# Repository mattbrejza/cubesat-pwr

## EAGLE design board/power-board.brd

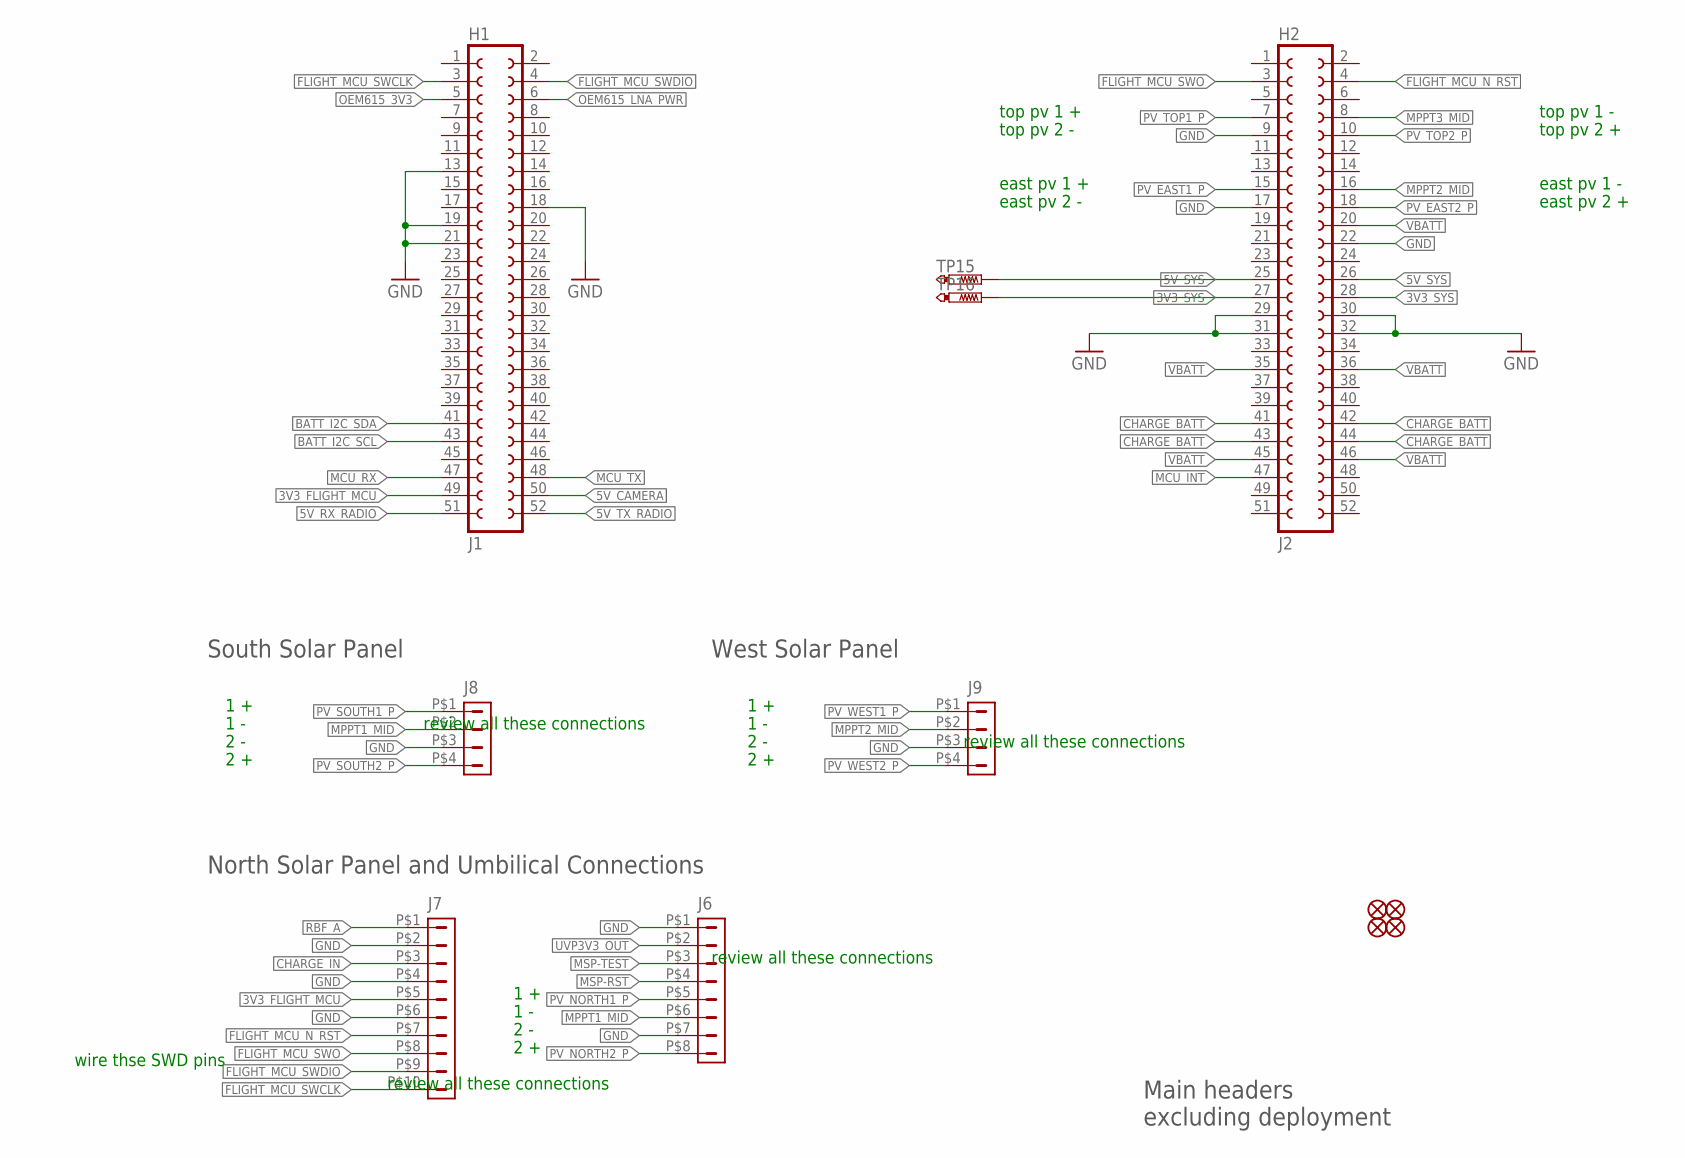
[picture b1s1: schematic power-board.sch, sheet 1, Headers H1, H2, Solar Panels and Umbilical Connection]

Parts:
FID1, FID2, FID3, FID4: FIDUCIAL1X2-STOP; FIDUCIAL-1X2-STOP
J1: H1; FE26-2
J2: H2; FE26-2
J6: DF13-8P-1.25DS
J7: DF13-10P-1.25DS
J8, J9: DF13-4P-1.25DS
TP15, TP16: PTR1TP09R; TP09R

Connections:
3V3_FLIGHT_MCU: J1.49, J7.P$5 (5); also elsewhere on the board
3V3_SYS: J2.27, J2.28, TP16.TP; also elsewhere on the board
5V_CAMERA: J1.50; also elsewhere on the board
5V_RX_RADIO: J1.51; also elsewhere on the board
5V_SYS: J2.25, J2.26, TP15.TP; also elsewhere on the board
5V_TX_RADIO: J1.52; also elsewhere on the board
BATT_I2C_SCL: J1.43; also elsewhere on the board
BATT_I2C_SDA: J1.41; also elsewhere on the board
CHARGE_BATT: J2.41, J2.42, J2.43, J2.44; also elsewhere on the board
CHARGE_IN: J7.P$3 (3); also elsewhere on the board
FLIGHT_MCU_N_RST: J2.4, J7.P$7 (7)
FLIGHT_MCU_SWCLK: J1.3, J7.P$10 (10)
FLIGHT_MCU_SWDIO: J1.4, J7.P$9 (9)
FLIGHT_MCU_SWO: J2.3, J7.P$8 (8)
GND: J1.13, J1.18, J1.19, J1.21, J2.9, J2.17, J2.22, J2.29, J2.30, J2.31, J2.32, J6.P$1 (1), J6.P$7 (7), J7.P$2 (2), J7.P$4 (4), J7.P$6 (6), J8.P$3 (3), J9.P$3 (3); also elsewhere on the board
MCU_INT: J2.47; also elsewhere on the board
MCU_RX: J1.47; also elsewhere on the board
MCU_TX: J1.48; also elsewhere on the board
MPPT1_MID: J6.P$6 (6), J8.P$2 (2); also elsewhere on the board
MPPT2_MID: J2.16, J9.P$2 (2); also elsewhere on the board
MPPT3_MID: J2.8; also elsewhere on the board
MSP-RST: J6.P$4 (4); also elsewhere on the board
MSP-TEST: J6.P$3 (3); also elsewhere on the board
OEM615_3V3: J1.5; also elsewhere on the board
OEM615_LNA_PWR: J1.6; also elsewhere on the board
PV_EAST1_P: J2.15; also elsewhere on the board
PV_EAST2_P: J2.18; also elsewhere on the board
PV_NORTH1_P: J6.P$5 (5); also elsewhere on the board
PV_NORTH2_P: J6.P$8 (8); also elsewhere on the board
PV_SOUTH1_P: J8.P$1 (1); also elsewhere on the board
PV_SOUTH2_P: J8.P$4 (4); also elsewhere on the board
PV_TOP1_P: J2.7; also elsewhere on the board
PV_TOP2_P: J2.10; also elsewhere on the board
PV_WEST1_P: J9.P$1 (1); also elsewhere on the board
PV_WEST2_P: J9.P$4 (4); also elsewhere on the board
RBF_A: J7.P$1 (1)
UVP3V3_OUT: J6.P$2 (2); also elsewhere on the board
VBATT: J2.20, J2.35, J2.36, J2.45, J2.46; also elsewhere on the board

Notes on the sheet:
South Solar Panel
West Solar Panel
North Solar Panel and Umbilical Connections
Main headers excluding deployment
review all these connections
top pv 1 -
east pv 1 -
east pv 2 +
top pv 2 +
wire thse SWD pins
top pv 1 +
top pv 2 -
east pv 1 +
east pv 2 -
1 +
1 -
2 +
2 -

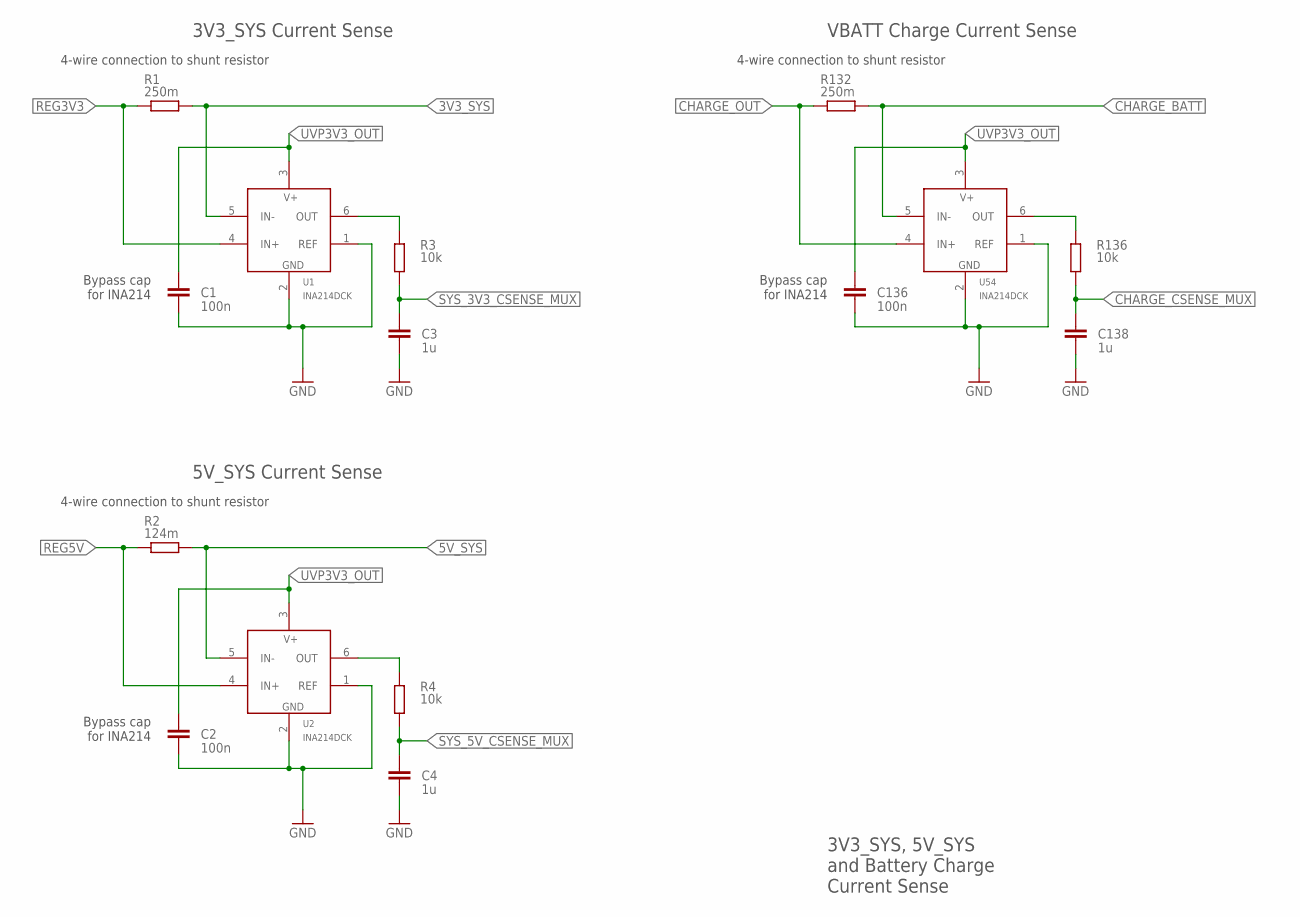
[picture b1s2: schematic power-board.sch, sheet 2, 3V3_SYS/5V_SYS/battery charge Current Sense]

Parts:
C1, C2, C136: 100n; C0603
C3, C4, C138: 1u; C0603
R1, R132: 250m; R1206
R2: 124m; R1206
R3, R4, R136: 10k; R0603
U1, U2, U54: INA214DCK; SC70-6

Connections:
3V3_SYS: R1.2, U1.5 (IN-); also elsewhere on the board
5V_SYS: R2.2, U2.5 (IN-); also elsewhere on the board
CHARGE_BATT: R132.2, U54.5 (IN-); also elsewhere on the board
CHARGE_CSENSE_MUX: C138.1, R136.1; also elsewhere on the board
CHARGE_OUT: R132.1, U54.4 (IN+); also elsewhere on the board
GND: C1.2, C2.2, C3.2, C4.2, C136.2, C138.2, U1.1 (REF), U1.2 (GND), U2.1 (REF), U2.2 (GND), U54.1 (REF), U54.2 (GND); also elsewhere on the board
unnamed: R3.2, U1.6 (OUT)
unnamed: R4.2, U2.6 (OUT)
unnamed: R136.2, U54.6 (OUT)
REG3V3: R1.1, U1.4 (IN+); also elsewhere on the board
REG5V: R2.1, U2.4 (IN+); also elsewhere on the board
SYS_3V3_CSENSE_MUX: C3.1, R3.1; also elsewhere on the board
SYS_5V_CSENSE_MUX: C4.1, R4.1; also elsewhere on the board
UVP3V3_OUT: C1.1, C2.1, C136.1, U1.3 (V+), U2.3 (V+), U54.3 (V+); also elsewhere on the board

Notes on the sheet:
4-wire connection to shunt resistor
Bypass cap for INA214
3V3_SYS, 5V_SYS and Battery Charge Current Sense
3V3_SYS Current Sense
5V_SYS Current Sense
VBATT Charge Current Sense

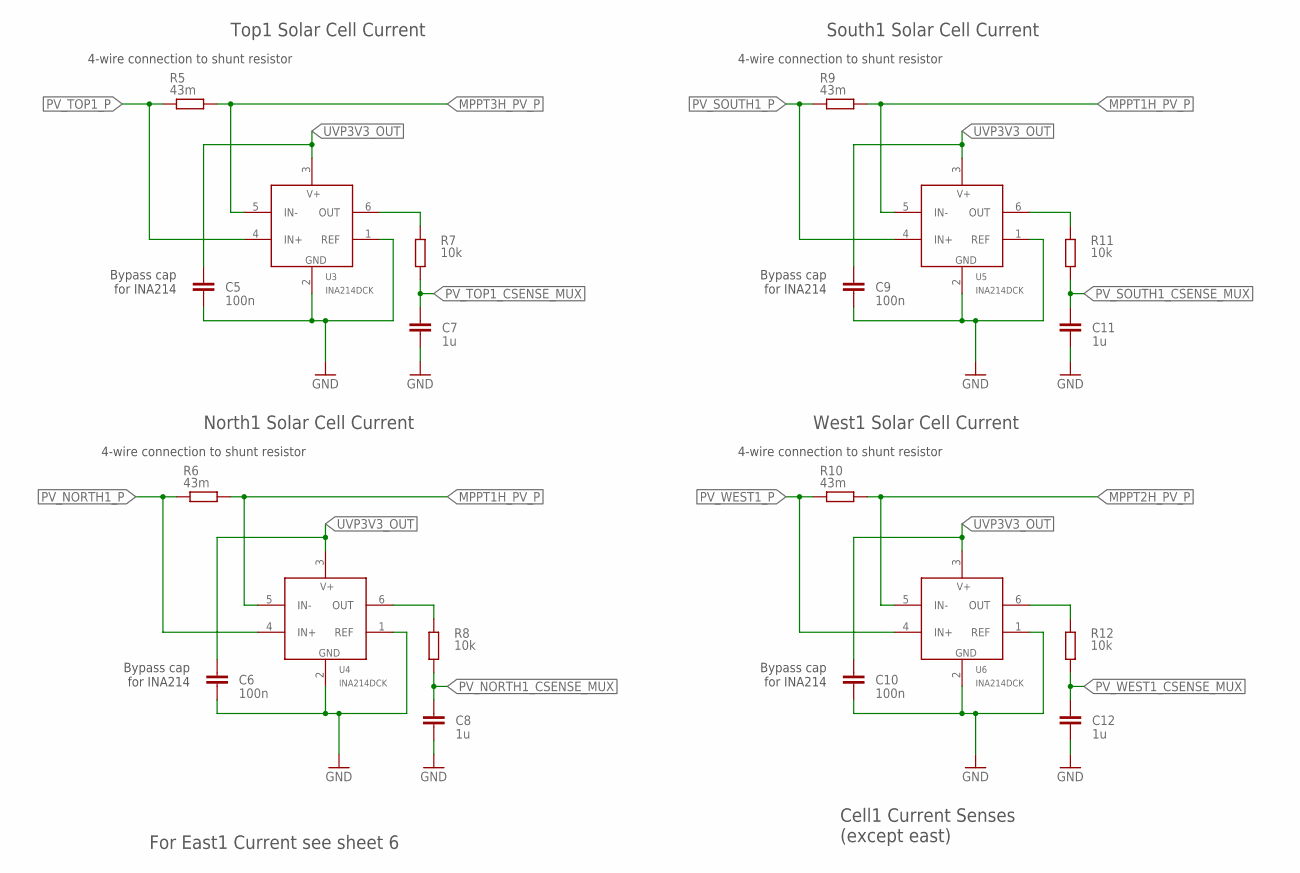
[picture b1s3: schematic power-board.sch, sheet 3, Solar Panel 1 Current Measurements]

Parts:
C5, C6, C9, C10: 100n; C0603
C7, C8, C11, C12: 1u; C0603
R5, R6, R9, R10: 43m; R1206
R7, R8, R11, R12: 10k; R0603
U3, U4, U5, U6: INA214DCK; SC70-6

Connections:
GND: C5.2, C6.2, C7.2, C8.2, C9.2, C10.2, C11.2, C12.2, U3.1 (REF), U3.2 (GND), U4.1 (REF), U4.2 (GND), U5.1 (REF), U5.2 (GND), U6.1 (REF), U6.2 (GND); also elsewhere on the board
MPPT1H_PV_P: R6.2, R9.2, U4.5 (IN-), U5.5 (IN-); also elsewhere on the board
MPPT2H_PV_P: R10.2, U6.5 (IN-); also elsewhere on the board
MPPT3H_PV_P: R5.2, U3.5 (IN-); also elsewhere on the board
unnamed: R7.2, U3.6 (OUT)
unnamed: R11.2, U5.6 (OUT)
unnamed: R8.2, U4.6 (OUT)
unnamed: R12.2, U6.6 (OUT)
PV_NORTH1_CSENSE_MUX: C8.1, R8.1; also elsewhere on the board
PV_NORTH1_P: R6.1, U4.4 (IN+); also elsewhere on the board
PV_SOUTH1_CSENSE_MUX: C11.1, R11.1; also elsewhere on the board
PV_SOUTH1_P: R9.1, U5.4 (IN+); also elsewhere on the board
PV_TOP1_CSENSE_MUX: C7.1, R7.1; also elsewhere on the board
PV_TOP1_P: R5.1, U3.4 (IN+); also elsewhere on the board
PV_WEST1_CSENSE_MUX: C12.1, R12.1; also elsewhere on the board
PV_WEST1_P: R10.1, U6.4 (IN+); also elsewhere on the board
UVP3V3_OUT: C5.1, C6.1, C9.1, C10.1, U3.3 (V+), U4.3 (V+), U5.3 (V+), U6.3 (V+); also elsewhere on the board

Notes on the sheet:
4-wire connection to shunt resistor
Bypass cap for INA214
Top1 Solar Cell Current
South1 Solar Cell Current
North1 Solar Cell Current
Cell1 Current Senses (except east)
West1 Solar Cell Current
For East1 Current see sheet 6

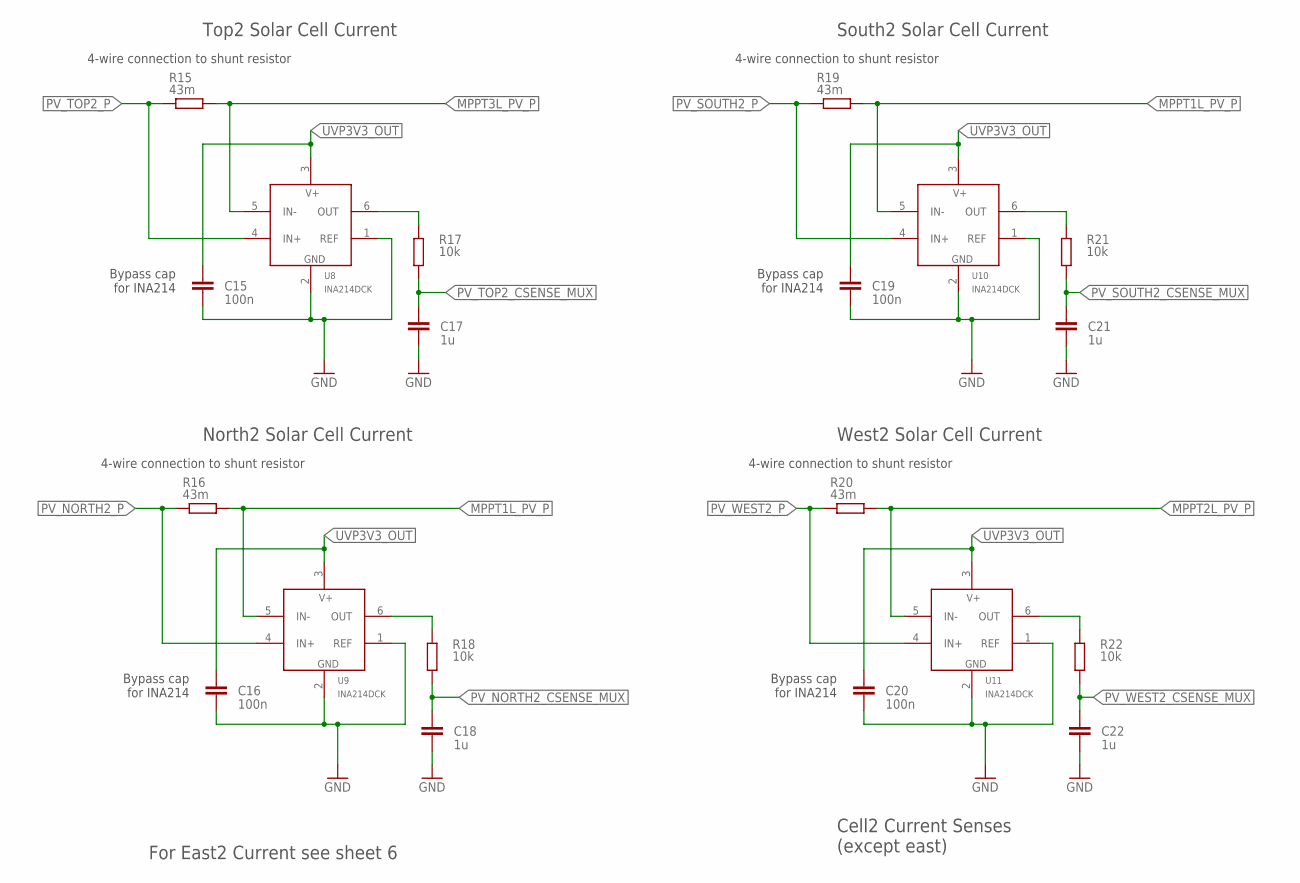
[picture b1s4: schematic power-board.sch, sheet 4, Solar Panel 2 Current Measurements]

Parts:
C15, C16, C19, C20: 100n; C0603
C17, C18, C21, C22: 1u; C0603
R15, R16, R19, R20: 43m; R1206
R17, R18, R21, R22: 10k; R0603
U8, U9, U10, U11: INA214DCK; SC70-6

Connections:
GND: C15.2, C16.2, C17.2, C18.2, C19.2, C20.2, C21.2, C22.2, U8.1 (REF), U8.2 (GND), U9.1 (REF), U9.2 (GND), U10.1 (REF), U10.2 (GND), U11.1 (REF), U11.2 (GND); also elsewhere on the board
MPPT1L_PV_P: R16.2, R19.2, U9.5 (IN-), U10.5 (IN-); also elsewhere on the board
MPPT2L_PV_P: R20.2, U11.5 (IN-); also elsewhere on the board
MPPT3L_PV_P: R15.2, U8.5 (IN-); also elsewhere on the board
unnamed: R17.2, U8.6 (OUT)
unnamed: R21.2, U10.6 (OUT)
unnamed: R18.2, U9.6 (OUT)
unnamed: R22.2, U11.6 (OUT)
PV_NORTH2_CSENSE_MUX: C18.1, R18.1; also elsewhere on the board
PV_NORTH2_P: R16.1, U9.4 (IN+); also elsewhere on the board
PV_SOUTH2_CSENSE_MUX: C21.1, R21.1; also elsewhere on the board
PV_SOUTH2_P: R19.1, U10.4 (IN+); also elsewhere on the board
PV_TOP2_CSENSE_MUX: C17.1, R17.1; also elsewhere on the board
PV_TOP2_P: R15.1, U8.4 (IN+); also elsewhere on the board
PV_WEST2_CSENSE_MUX: C22.1, R22.1; also elsewhere on the board
PV_WEST2_P: R20.1, U11.4 (IN+); also elsewhere on the board
UVP3V3_OUT: C15.1, C16.1, C19.1, C20.1, U8.3 (V+), U9.3 (V+), U10.3 (V+), U11.3 (V+); also elsewhere on the board

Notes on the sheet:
4-wire connection to shunt resistor
Bypass cap for INA214
Top2 Solar Cell Current
South2 Solar Cell Current
North2 Solar Cell Current
West2 Solar Cell Current
Cell2 Current Senses (except east)
For East2 Current see sheet 6

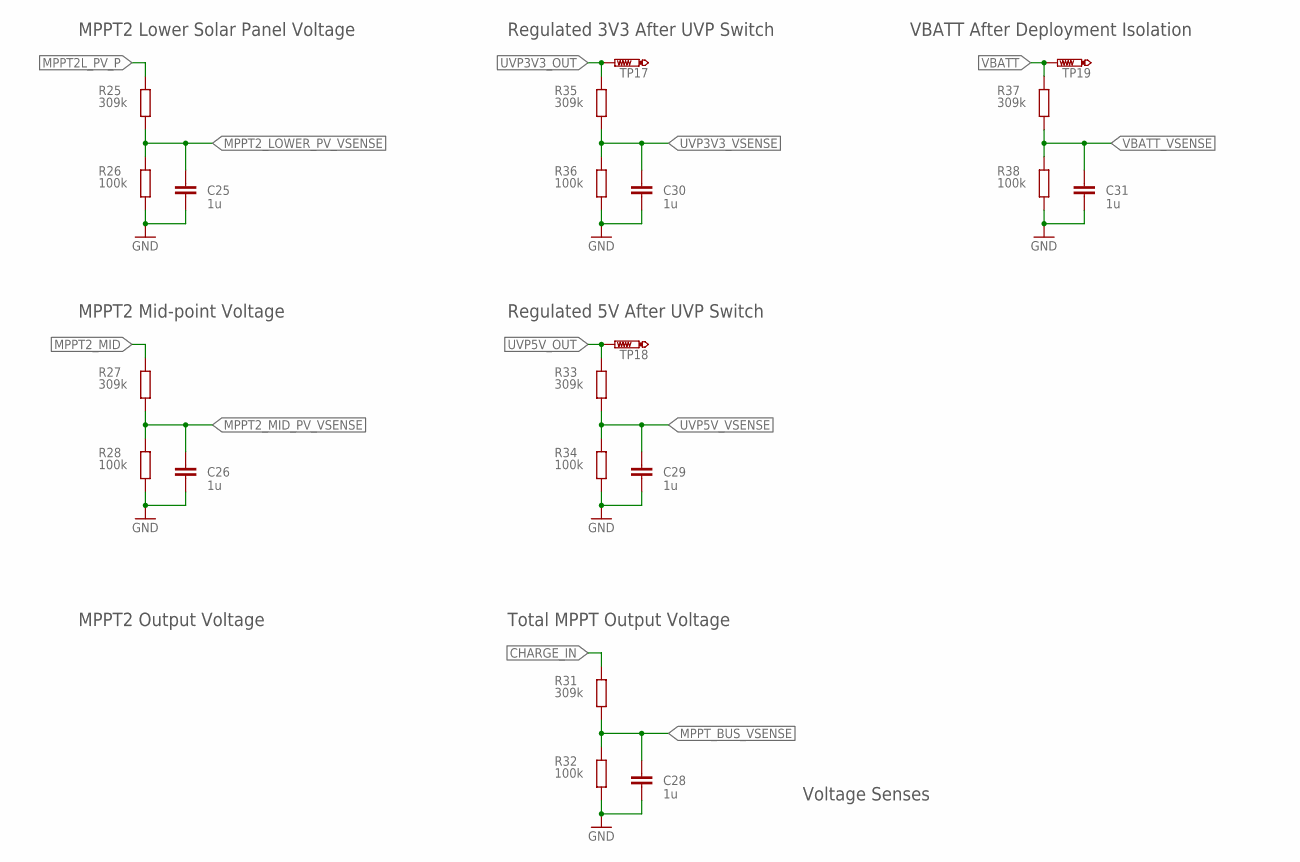
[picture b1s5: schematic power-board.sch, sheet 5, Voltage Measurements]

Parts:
C25, C26, C28, C29, C30, C31: 1u; C0603
R25, R27, R31, R33, R35, R37: 309k; R0603
R26, R28, R32, R34, R36, R38: 100k; R0603
TP17, TP18, TP19: PTR1TP09R; TP09R

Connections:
CHARGE_IN: R31.2; also elsewhere on the board
GND: C25.2, C26.2, C28.2, C29.2, C30.2, C31.2, R26.1, R28.1, R32.1, R34.1, R36.1, R38.1; also elsewhere on the board
MPPT2L_PV_P: R25.2; also elsewhere on the board
MPPT2_LOWER_PV_VSENSE: C25.1, R25.1, R26.2; also elsewhere on the board
MPPT2_MID: R27.2; also elsewhere on the board
MPPT2_MID_PV_VSENSE: C26.1, R27.1, R28.2; also elsewhere on the board
MPPT_BUS_VSENSE: C28.1, R31.1, R32.2; also elsewhere on the board
UVP3V3_OUT: R35.2, TP17.TP; also elsewhere on the board
UVP3V3_VSENSE: C30.1, R35.1, R36.2; also elsewhere on the board
UVP5V_OUT: R33.2, TP18.TP; also elsewhere on the board
UVP5V_VSENSE: C29.1, R33.1, R34.2; also elsewhere on the board
VBATT: R37.2, TP19.TP; also elsewhere on the board
VBATT_VSENSE: C31.1, R37.1, R38.2; also elsewhere on the board

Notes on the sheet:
MPPT2 Lower Solar Panel Voltage
MPPT2 Mid-point Voltage
Regulated 5V After UVP Switch
Regulated 3V3 After UVP Switch
MPPT2 Output Voltage
Total MPPT Output Voltage
VBATT After Deployment Isolation
Voltage Senses

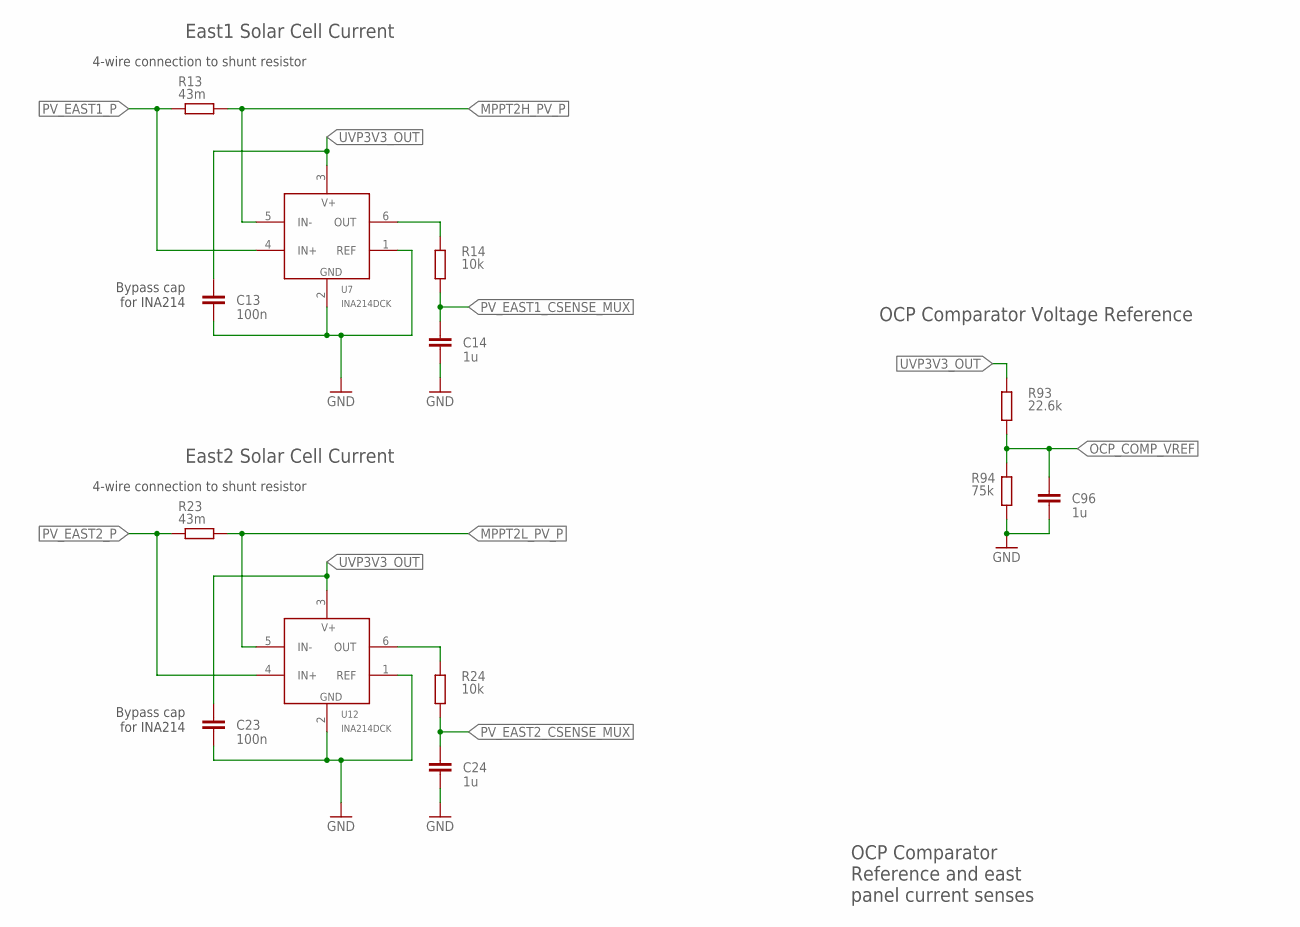
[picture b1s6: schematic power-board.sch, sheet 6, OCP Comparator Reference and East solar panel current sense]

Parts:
C13, C23: 100n; C0603
C14, C24, C96: 1u; C0603
R13, R23: 43m; R1206
R14, R24: 10k; R0603
R93: 22.6k; R0603
R94: 75k; R0603
U7, U12: INA214DCK; SC70-6

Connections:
GND: C13.2, C14.2, C23.2, C24.2, C96.2, R94.1, U7.1 (REF), U7.2 (GND), U12.1 (REF), U12.2 (GND); also elsewhere on the board
MPPT2H_PV_P: R13.2, U7.5 (IN-); also elsewhere on the board
MPPT2L_PV_P: R23.2, U12.5 (IN-); also elsewhere on the board
unnamed: R14.2, U7.6 (OUT)
unnamed: R24.2, U12.6 (OUT)
OCP_COMP_VREF: C96.1, R93.1, R94.2; also elsewhere on the board
PV_EAST1_CSENSE_MUX: C14.1, R14.1; also elsewhere on the board
PV_EAST1_P: R13.1, U7.4 (IN+); also elsewhere on the board
PV_EAST2_CSENSE_MUX: C24.1, R24.1; also elsewhere on the board
PV_EAST2_P: R23.1, U12.4 (IN+); also elsewhere on the board
UVP3V3_OUT: C13.1, C23.1, R93.2, U7.3 (V+), U12.3 (V+); also elsewhere on the board

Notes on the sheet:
4-wire connection to shunt resistor
Bypass cap for INA214
OCP Comparator Reference and east panel current senses
East1 Solar Cell Current
East2 Solar Cell Current
OCP Comparator Voltage Reference

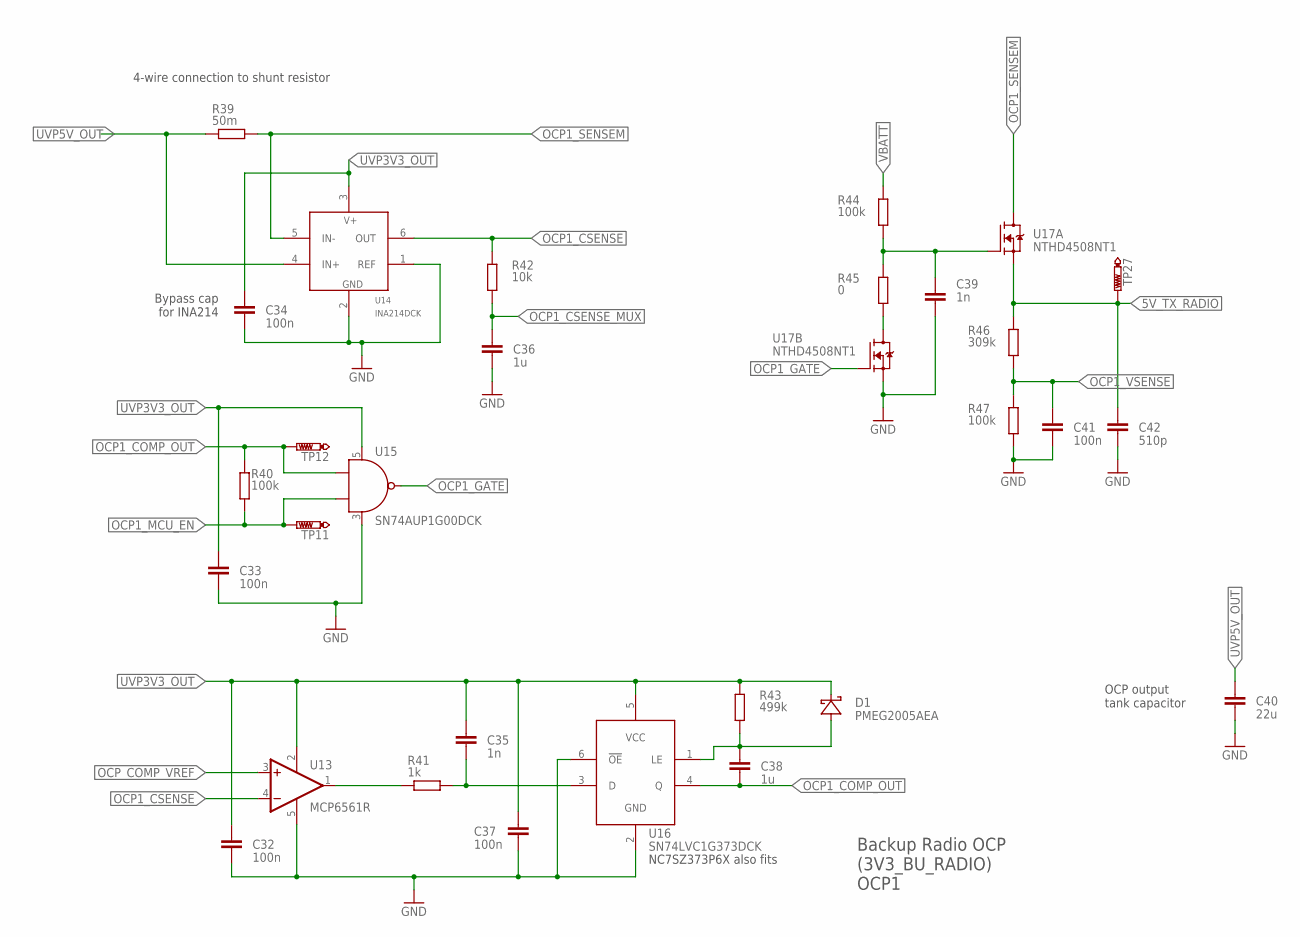
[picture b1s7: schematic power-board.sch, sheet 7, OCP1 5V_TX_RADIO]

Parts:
C32, C33, C34, C37, C41: 100n; C0603
C35, C39: 1n; C0603
C36, C38: 1u; C0603
C40: 22u; C1210
C42: 510p; C0603
D1: PMEG2005AEA; SOD-323
R39: 50m; R1206
R40, R44, R47: 100k; R0603
R41: 1k; R0603
R42: 10k; R0603
R43: 499k; R0603
R45: 0; R0603
R46: 309k; R0603
TP11, TP12, TP27: PTR1TP09R; TP09R
U13: MCP6561R; SOT23-5
U14: INA214DCK; SC70-6
U15: SN74AUP1G00DCK; SC70-5
U16: SN74LVC1G373DCK; SC70-6
U17: NTHD4508NT1; CHIPFET-1206A-S2

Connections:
5V_TX_RADIO: C42.1, R46.2, TP27.TP, U17.1 (S); also elsewhere on the board
GND: C32.2, C33.2, C34.2, C36.2, C37.2, C39.2, C40.2, C41.2, C42.2, R47.1, U13.5 (V-), U14.1 (REF), U14.2 (GND), U15.3 (V-), U16.2 (GND), U16.6 (!OE), U17.3 (S); also elsewhere on the board
unnamed: C39.1, R44.1, R45.2, U17.2 (G)
unnamed: R45.1, U17.5 (D), U17.6 (D)
unnamed: C35.1, R41.2, U16.3 (D)
unnamed: R41.1, U13.1 (OUT)
unnamed: C38.1, D1.2 (A), R43.1, U16.1 (LE)
OCP1_COMP_OUT: C38.2, R40.2, TP12.TP, U15.1 (A), U16.4 (Q)
OCP1_CSENSE: R42.2, U13.4 (-IN), U14.6 (OUT)
OCP1_CSENSE_MUX: C36.1, R42.1; also elsewhere on the board
OCP1_GATE: U15.4 (Y), U17.4 (G)
OCP1_MCU_EN: R40.1, TP11.TP, U15.2 (B); also elsewhere on the board
OCP1_SENSEM: R39.2, U14.5 (IN-), U17.7 (D), U17.8 (D)
OCP1_VSENSE: C41.1, R46.1, R47.2; also elsewhere on the board
OCP_COMP_VREF: U13.3 (+IN); also elsewhere on the board
UVP3V3_OUT: C32.1, C33.1, C34.1, C35.2, C37.1, D1.1 (C), R43.2, U13.2 (V+), U14.3 (V+), U15.5 (V+), U16.5 (VCC); also elsewhere on the board
UVP5V_OUT: C40.1, R39.1, U14.4 (IN+); also elsewhere on the board
VBATT: R44.2; also elsewhere on the board

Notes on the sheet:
NC7SZ373P6X also fits
4-wire connection to shunt resistor
Bypass cap for INA214
OCP output tank capacitor
Backup Radio OCP (3V3_BU_RADIO) OCP1

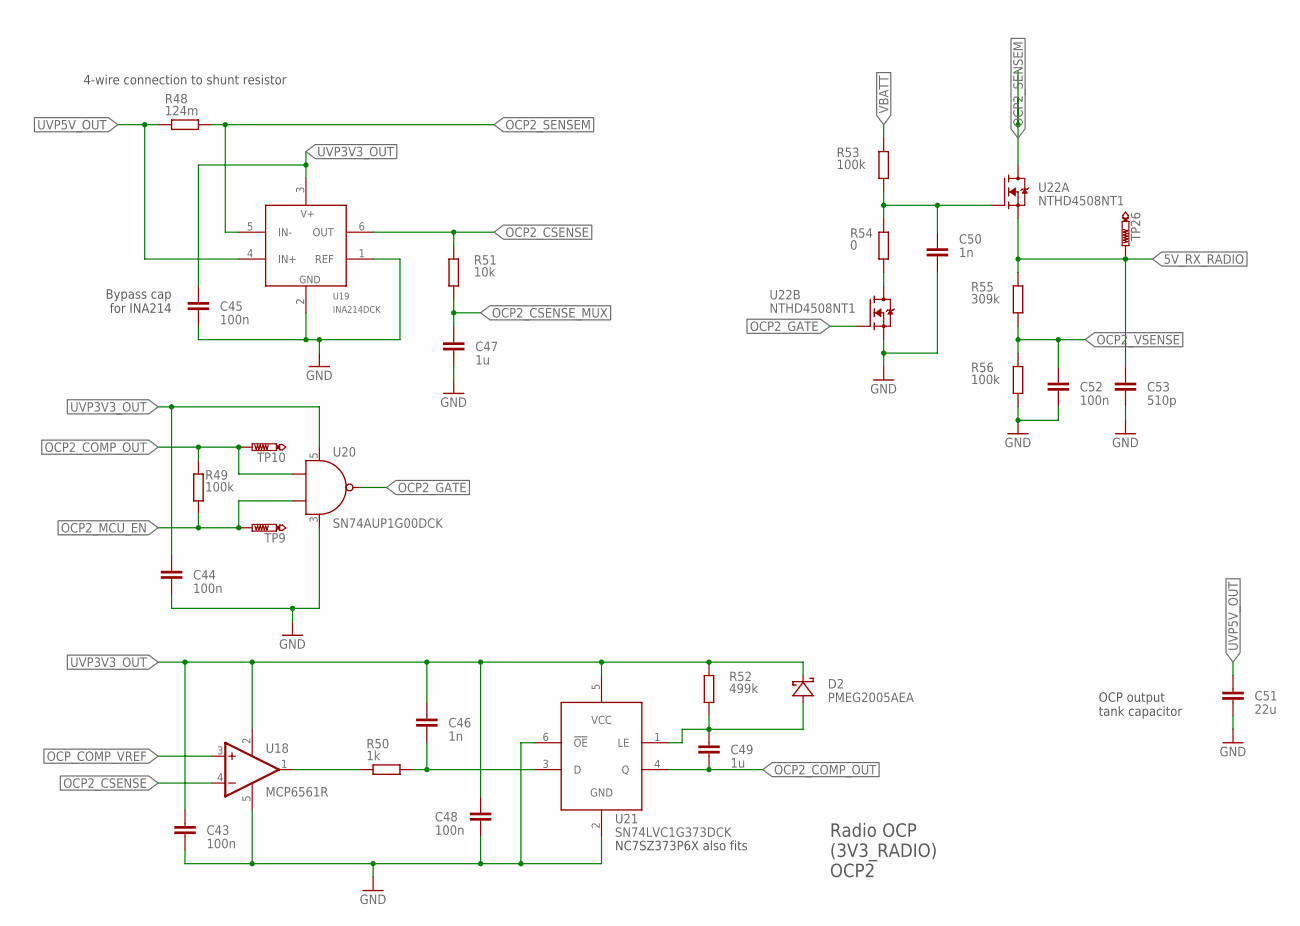
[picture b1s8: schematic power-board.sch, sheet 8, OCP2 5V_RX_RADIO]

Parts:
C43, C44, C45, C48, C52: 100n; C0603
C46, C50: 1n; C0603
C47, C49: 1u; C0603
C51: 22u; C1210
C53: 510p; C0603
D2: PMEG2005AEA; SOD-323
R48: 124m; R1206
R49, R53, R56: 100k; R0603
R50: 1k; R0603
R51: 10k; R0603
R52: 499k; R0603
R54: 0; R0603
R55: 309k; R0603
TP9, TP10, TP26: PTR1TP09R; TP09R
U18: MCP6561R; SOT23-5
U19: INA214DCK; SC70-6
U20: SN74AUP1G00DCK; SC70-5
U21: SN74LVC1G373DCK; SC70-6
U22: NTHD4508NT1; CHIPFET-1206A-S2

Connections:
5V_RX_RADIO: C53.1, R55.2, TP26.TP, U22.1 (S); also elsewhere on the board
GND: C43.2, C44.2, C45.2, C47.2, C48.2, C50.2, C51.2, C52.2, C53.2, R56.1, U18.5 (V-), U19.1 (REF), U19.2 (GND), U20.3 (V-), U21.2 (GND), U21.6 (!OE), U22.3 (S); also elsewhere on the board
unnamed: R54.1, U22.5 (D), U22.6 (D)
unnamed: C46.1, R50.2, U21.3 (D)
unnamed: R50.1, U18.1 (OUT)
unnamed: C49.1, D2.2 (A), R52.1, U21.1 (LE)
unnamed: C50.1, R53.1, R54.2, U22.2 (G)
OCP2_COMP_OUT: C49.2, R49.2, TP10.TP, U20.1 (A), U21.4 (Q)
OCP2_CSENSE: R51.2, U18.4 (-IN), U19.6 (OUT)
OCP2_CSENSE_MUX: C47.1, R51.1; also elsewhere on the board
OCP2_GATE: U20.4 (Y), U22.4 (G)
OCP2_MCU_EN: R49.1, TP9.TP, U20.2 (B); also elsewhere on the board
OCP2_SENSEM: R48.2, U19.5 (IN-), U22.7 (D), U22.8 (D)
OCP2_VSENSE: C52.1, R55.1, R56.2; also elsewhere on the board
OCP_COMP_VREF: U18.3 (+IN); also elsewhere on the board
UVP3V3_OUT: C43.1, C44.1, C45.1, C46.2, C48.1, D2.1 (C), R52.2, U18.2 (V+), U19.3 (V+), U20.5 (V+), U21.5 (VCC); also elsewhere on the board
UVP5V_OUT: C51.1, R48.1, U19.4 (IN+); also elsewhere on the board
VBATT: R53.2; also elsewhere on the board

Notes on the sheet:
NC7SZ373P6X also fits
4-wire connection to shunt resistor
Bypass cap for INA214
OCP output tank capacitor
Radio OCP (3V3_RADIO) OCP2

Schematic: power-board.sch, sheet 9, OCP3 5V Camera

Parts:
C54, C55, C56, C59, C63: 100n; C0603
C57, C61: 1n; C0603
C58, C60: 1u; C0603
C62: 22u; C1210
C64: 510p; C0603
D3: PMEG2005AEA; SOD-323
R57: 124m; R1206
R58, R62, R65: 100k; R0603
R59: 1k; R0603
R60: 10k; R0603
R61: 499k; R0603
R63: 0; R0603
R64: 309k; R0603
TP7, TP8, TP25: PTR1TP09R; TP09R
U23: MCP6561R; SOT23-5
U24: INA214DCK; SC70-6
U25: SN74AUP1G00DCK; SC70-5
U26: SN74LVC1G373DCK; SC70-6
U27: NTHD4508NT1; CHIPFET-1206A-S2

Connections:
5V_CAMERA: C64.1, R64.2, TP25.TP, U27.1 (S); also elsewhere on the board
GND: C54.2, C55.2, C56.2, C58.2, C59.2, C61.2, C62.2, C63.2, C64.2, R65.1, U23.5 (V-), U24.1 (REF), U24.2 (GND), U25.3 (V-), U26.2 (GND), U26.6 (!OE), U27.3 (S); also elsewhere on the board
unnamed: R63.1, U27.5 (D), U27.6 (D)
unnamed: C57.1, R59.2, U26.3 (D)
unnamed: R59.1, U23.1 (OUT)
unnamed: C60.1, D3.2 (A), R61.1, U26.1 (LE)
unnamed: C61.1, R62.1, R63.2, U27.2 (G)
OCP3_COMP_OUT: C60.2, R58.2, TP8.TP, U25.1 (A), U26.4 (Q)
OCP3_CSENSE: R60.2, U23.4 (-IN), U24.6 (OUT)
OCP3_CSENSE_MUX: C58.1, R60.1; also elsewhere on the board
OCP3_GATE: U25.4 (Y), U27.4 (G)
OCP3_MCU_EN: R58.1, TP7.TP, U25.2 (B); also elsewhere on the board
OCP3_SENSEM: R57.2, U24.5 (IN-), U27.7 (D), U27.8 (D)
OCP3_VSENSE: C63.1, R64.1, R65.2; also elsewhere on the board
OCP_COMP_VREF: U23.3 (+IN); also elsewhere on the board
UVP3V3_OUT: C54.1, C55.1, C56.1, C57.2, C59.1, D3.1 (C), R61.2, U23.2 (V+), U24.3 (V+), U25.5 (V+), U26.5 (VCC); also elsewhere on the board
UVP5V_OUT: C62.1, R57.1, U24.4 (IN+); also elsewhere on the board
VBATT: R62.2; also elsewhere on the board

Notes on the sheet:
NC7SZ373P6X also fits
4-wire connection to shunt resistor
Bypass cap for INA214
OCP output tank capacitor
Camera OCP (5V_CAMERA) OCP3

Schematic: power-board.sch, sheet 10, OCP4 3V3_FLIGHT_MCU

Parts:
C65, C66, C67, C70, C74: 100n; C0603
C68, C72: 1n; C0603
C69, C71: 1u; C0603
C73: 22u; C1210
C75: 510p; C0603
D4: PMEG2005AEA; SOD-323
R66: 442m; R1206
R67, R71, R74: 100k; R0603
R68: 1k; R0603
R69: 10k; R0603
R70: 499k; R0603
R72: 0; R0603
R73: 309k; R0603
TP5, TP6, TP24: PTR1TP09R; TP09R
U28: MCP6561R; SOT23-5
U29: INA214DCK; SC70-6
U30: SN74AUP1G00DCK; SC70-5
U31: SN74LVC1G373DCK; SC70-6
U32: NTHD4508NT1; CHIPFET-1206A-S2

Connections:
3V3_FLIGHT_MCU: C75.1, R73.2, TP24.TP, U32.1 (S); also elsewhere on the board
GND: C65.2, C66.2, C67.2, C69.2, C70.2, C72.2, C73.2, C74.2, C75.2, R74.1, U28.5 (V-), U29.1 (REF), U29.2 (GND), U30.3 (V-), U31.2 (GND), U31.6 (!OE), U32.3 (S); also elsewhere on the board
unnamed: R72.1, U32.5 (D), U32.6 (D)
unnamed: C68.1, R68.2, U31.3 (D)
unnamed: R68.1, U28.1 (OUT)
unnamed: C71.1, D4.2 (A), R70.1, U31.1 (LE)
unnamed: C72.1, R71.1, R72.2, U32.2 (G)
OCP4_COMP_OUT: C71.2, R67.2, TP6.TP, U30.1 (A), U31.4 (Q)
OCP4_CSENSE: R69.2, U28.4 (-IN), U29.6 (OUT)
OCP4_CSENSE_MUX: C69.1, R69.1; also elsewhere on the board
OCP4_GATE: U30.4 (Y), U32.4 (G)
OCP4_MCU_EN: R67.1, TP5.TP, U30.2 (B); also elsewhere on the board
OCP4_SENSEM: R66.2, U29.5 (IN-), U32.7 (D), U32.8 (D)
OCP4_VSENSE: C74.1, R73.1, R74.2; also elsewhere on the board
OCP_COMP_VREF: U28.3 (+IN); also elsewhere on the board
UVP3V3_OUT: C65.1, C66.1, C67.1, C68.2, C70.1, C73.1, D4.1 (C), R66.1, R70.2, U28.2 (V+), U29.3 (V+), U29.4 (IN+), U30.5 (V+), U31.5 (VCC); also elsewhere on the board
VBATT: R71.2; also elsewhere on the board

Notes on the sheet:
NC7SZ373P6X also fits
4-wire connection to shunt resistor
Bypass cap for INA214
OCP output tank capacitor
Flight MCU OCP (3V3_FLIGHT_MCU) OCP4
100uA
0.9uA
10uA

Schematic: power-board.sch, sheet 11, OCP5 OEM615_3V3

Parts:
C76, C77, C78, C81, C85: 100n; C0603
C79: 470n; C0603
C80, C82: 1u; C0603
C83: 1n; C0603
C84: 22u; C1210
C86: 510p; C0603
D5: PMEG2005AEA; SOD-323
R75: 50m; R1206
R76, R80, R83: 100k; R0603
R77: 1k; R0603
R78: 10k; R0603
R79: 499k; R0603
R81: 0; R0603
R82: 309k; R0603
TP3, TP4, TP23: PTR1TP09R; TP09R
U33: MCP6561R; SOT23-5
U34: INA214DCK; SC70-6
U35: SN74AUP1G00DCK; SC70-5
U36: SN74LVC1G373DCK; SC70-6
U37: NTHD4508NT1; CHIPFET-1206A-S2

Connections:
GND: C76.2, C77.2, C78.2, C80.2, C81.2, C83.2, C84.2, C85.2, C86.2, R83.1, U33.5 (V-), U34.1 (REF), U34.2 (GND), U35.3 (V-), U36.2 (GND), U36.6 (!OE), U37.3 (S); also elsewhere on the board
unnamed: R81.1, U37.5 (D), U37.6 (D)
unnamed: C79.1, R77.2, U36.3 (D)
unnamed: R77.1, U33.1 (OUT)
unnamed: C82.1, D5.2 (A), R79.1, U36.1 (LE)
unnamed: C83.1, R80.1, R81.2, U37.2 (G)
OCP5_COMP_OUT: C82.2, R76.2, TP4.TP, U35.1 (A), U36.4 (Q)
OCP5_CSENSE: R78.2, U33.4 (-IN), U34.6 (OUT)
OCP5_CSENSE_MUX: C80.1, R78.1; also elsewhere on the board
OCP5_GATE: U35.4 (Y), U37.4 (G)
OCP5_MCU_EN: R76.1, TP3.TP, U35.2 (B); also elsewhere on the board
OCP5_SENSEM: R75.2, U34.5 (IN-), U37.7 (D), U37.8 (D)
OCP5_VSENSE: C85.1, R82.1, R83.2; also elsewhere on the board
OCP_COMP_VREF: U33.3 (+IN); also elsewhere on the board
OEM615_3V3: C86.1, R82.2, TP23.TP, U37.1 (S); also elsewhere on the board
UVP3V3_OUT: C76.1, C77.1, C78.1, C79.2, C81.1, C84.1, D5.1 (C), R75.1, R79.2, U33.2 (V+), U34.3 (V+), U34.4 (IN+), U35.5 (V+), U36.5 (VCC); also elsewhere on the board
VBATT: R80.2; also elsewhere on the board

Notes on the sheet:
NC7SZ373P6X also fits
4-wire connection to shunt resistor
Bypass cap for INA214
OCP output tank capacitor
OEM615 OCP (OEM615_3V3) OCP5

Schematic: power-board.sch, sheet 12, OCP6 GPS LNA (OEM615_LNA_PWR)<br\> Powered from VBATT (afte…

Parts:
C87, C88, C89, C92, C94: 100n; C0603
C90: 1n; C0603
C91, C93: 1u; C0603
C95: 22u; C1210
D6: PMEG2005AEA; SOD-323
R84: 124m; R1206
R85, R92: 100k; R0603
R86: 1k; R0603
R87: 10k; R0603
R88: 499k; R0603
R89: 499; R0603
R90: 0; R0603
R91: 309k; R0603
TP1, TP2, TP22: PTR1TP09R; TP09R
U38: MCP6561R; SOT23-5
U39: INA214DCK; SC70-6
U40: SN74AUP1T08DCK; SC70-5
U41: SN74LVC1G373DCK; SC70-6
U42: FDS8858CZ; SO8

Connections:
GND: C87.2, C88.2, C89.2, C91.2, C92.2, C94.2, C95.2, R92.1, U38.5 (V-), U39.1 (REF), U39.2 (GND), U40.3 (V-), U41.2 (GND), U41.6 (!OE), U42.1 (S); also elsewhere on the board
unnamed: C90.1, R86.2, U41.3 (D)
unnamed: R86.1, U38.1 (OUT)
unnamed: C93.1, D6.2 (A), R88.1, U41.1 (LE)
unnamed: R89.2, R90.2, U42.4 (G)
unnamed: R90.1, U42.7 (D), U42.8 (D)
OCP6_COMP_OUT: C93.2, R85.2, TP2.TP, U40.1 (A), U41.4 (Q)
OCP6_CSENSE: R87.2, U38.4 (-IN), U39.6 (OUT)
OCP6_CSENSE_MUX: C91.1, R87.1; also elsewhere on the board
OCP6_GATE: U40.4 (Y), U42.2 (G)
OCP6_MCU_EN: R85.1, TP1.TP, U40.2 (B); also elsewhere on the board
OCP6_SENSEM: R84.2, R89.1, U39.5 (IN-), U42.3 (S)
OCP6_VSENSE: C94.1, R91.1, R92.2; also elsewhere on the board
OCP_COMP_VREF: U38.3 (+IN); also elsewhere on the board
OEM615_LNA_PWR: R91.2, TP22.TP, U42.5 (D), U42.6 (D); also elsewhere on the board
UVP3V3_OUT: C87.1, C88.1, C89.1, C90.2, C92.1, D6.1 (C), R88.2, U38.2 (V+), U39.3 (V+), U40.5 (V+), U41.5 (VCC); also elsewhere on the board
VBATT: C95.1, R84.1, U39.4 (IN+); also elsewhere on the board

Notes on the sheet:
NC7SZ373P6X also fits
4-wire connection to shunt resistor
Bypass cap for INA214
OCP output tank capacitor
OEM615 LNA OCP (OEM615_LNA_PWR) OCP6

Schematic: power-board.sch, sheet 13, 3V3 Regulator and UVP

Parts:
C97, C103: 10n; C0603
C98: 100n; C0603
C99: 10u; C1206
C100: 0.1u; C0603
C101: 3.3n; C0603
C102: 22u; C1210
L1: 2.2u; VISHAY-INDUCTOR
R95: 14.5k; R0603
R96: 10.2k; R0603
R97: 12.4k; R0603
R98: 124k; R0603
R99, R100: 100k; R0603
R101: 0; R0603
R140: 4.02k; R0603
TP13, TP21: PTR1TP09R; TP09R
U43: TLV3491AIDBV; SOT23-5
U44: TPS62132RGT; RGT.16
U45: FDS8858CZ; SO8

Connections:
GND: C97.2, C98.2, C99.2, C100.2, C101.1, C102.2, C103.2, R96.1, R98.1, U43.2 (V-), U44.5 (FB), U44.6 (AGND), U44.8 (DEF), U44.15 (PGND), U44.16 (PGND), U44.PAD (AGND), U45.1 (S); also elsewhere on the board
unnamed: C101.2, U44.9 (SS/TR)
unnamed: L1.1, U44.1 (SW), U44.2 (SW), U44.3 (SW)
unnamed: R101.1, U45.7 (D), U45.8 (D)
unnamed: R95.2, R96.2, R140.1
unnamed: R99.1, R140.2, U43.3 (+IN)
unnamed: R100.2, R101.2, U45.4 (G)
unnamed: R97.1, R98.2, U43.4 (-IN)
REG3V3: C98.1, C102.1, C103.1, L1.2, R97.2, R100.1, TP21.TP, U43.5 (V+), U44.7 (FSW), U44.14 (VOS), U45.3 (S); also elsewhere on the board
UVP3V3_GATE: R99.2, TP13.TP, U43.1 (OUT), U45.2 (G)
UVP3V3_OUT: U45.5 (D), U45.6 (D); also elsewhere on the board
VBATT: C97.1, C99.1, C100.1, R95.1, U44.10 (AVIN), U44.11 (PVIN), U44.12 (PVIN), U44.13 (EN); also elsewhere on the board

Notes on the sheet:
Application circuits taken from TPS62130 Datasheet Fig. 44.
FSW = High for 1.25MHz operation. Connect FSW to VOUT or PG.
See Fig. 50 for layout
3A Buck Regulators
TLV3491 bypass
3V3 Regulator and UVP
